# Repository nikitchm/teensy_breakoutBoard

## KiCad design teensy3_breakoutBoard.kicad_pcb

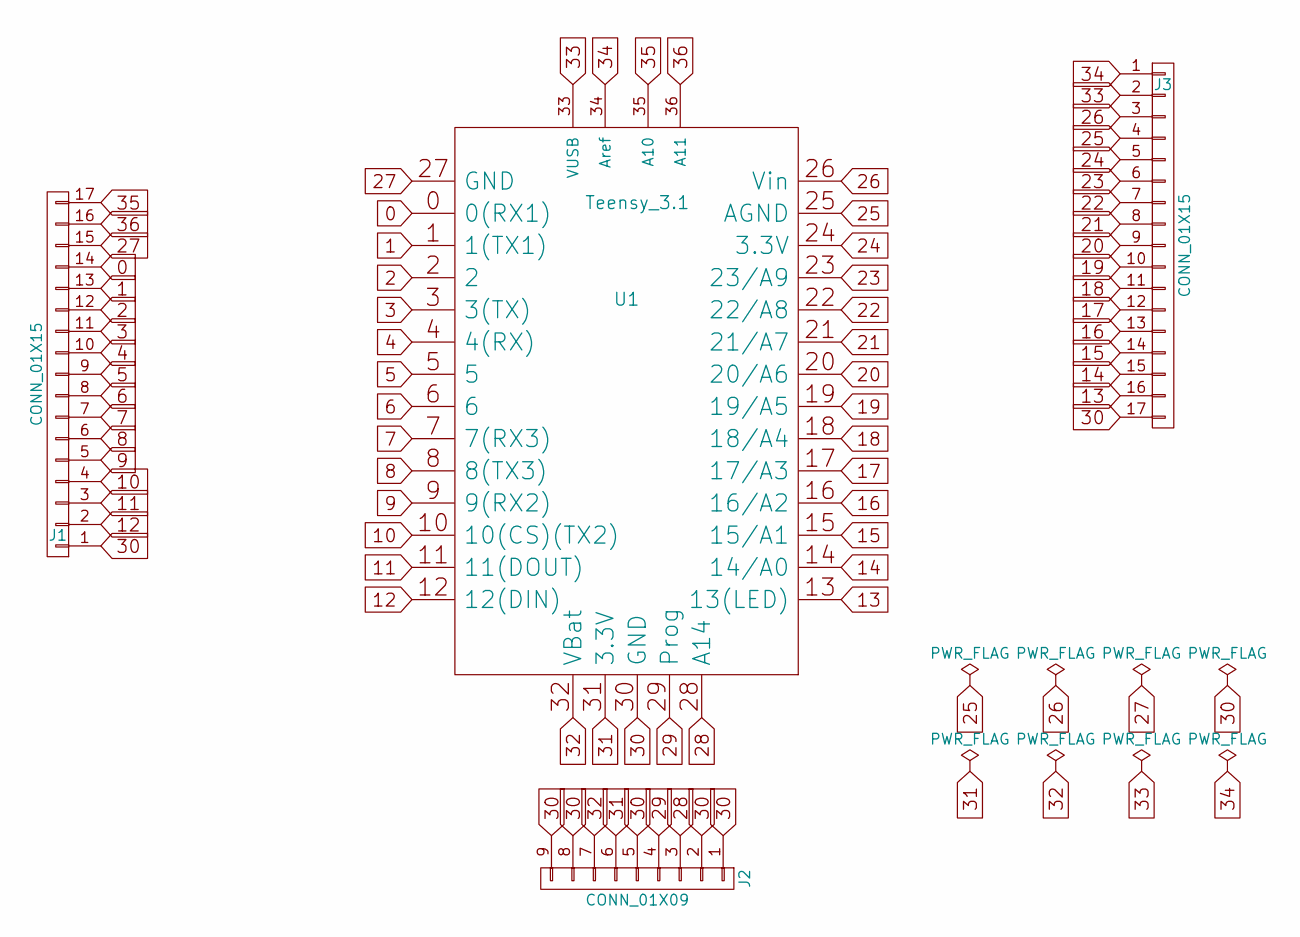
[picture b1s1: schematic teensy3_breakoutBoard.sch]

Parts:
J1, J3: CONN_01X15; Pin_Header_Straight_1x17_Pitch2.54mm
J2: CONN_01X09; Pin_Header_Straight_1x09_Pitch2.54mm
U1: Teensy_3.1; Teensy-3.1

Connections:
0: J1.14, U1.0 (0(RX1))
1: J1.13, U1.1 (1(TX1))
2: J1.12, U1.2
3: J1.11, U1.3 (3(TX))
4: J1.10, U1.4 (4(RX))
5: J1.9, U1.5
6: J1.8, U1.6
7: J1.7, U1.7 (7(RX3))
8: J1.6, U1.8 (8(TX3))
9: J1.5, U1.9 (9(RX2))
10: J1.4, U1.10 (10(CS)(TX2))
11: J1.3, U1.11 (11(DOUT))
12: J1.2, U1.12 (12(DIN))
13: J3.16, U1.13 (13(LED))
14: J3.15, U1.14 (14/A0)
15: J3.14, U1.15 (15/A1)
16: J3.13, U1.16 (16/A2)
17: J3.12, U1.17 (17/A3)
18: J3.11, U1.18 (18/A4)
19: J3.10, U1.19 (19/A5)
20: J3.9, U1.20 (20/A6)
21: J3.8, U1.21 (21/A7)
22: J3.7, U1.22 (22/A8)
23: J3.6, U1.23 (23/A9)
24: J3.5, U1.24 (3.3V)
25: J3.4, U1.25 (AGND)
26: J3.3, U1.26 (Vin)
27: J1.15, U1.27 (GND)
28: J2.3, U1.28 (A14)
29: J2.4, U1.29 (Prog)
30: J1.1, J2.1, J2.2, J2.5, J2.8, J2.9, J3.17, U1.30 (GND)
31: J2.6, U1.31 (3.3V)
32: J2.7, U1.32 (VBat)
33: J3.2, U1.33 (VUSB)
34: J3.1, U1.34 (Aref)
35: J1.17, U1.35 (A10)
36: J1.16, U1.36 (A11)

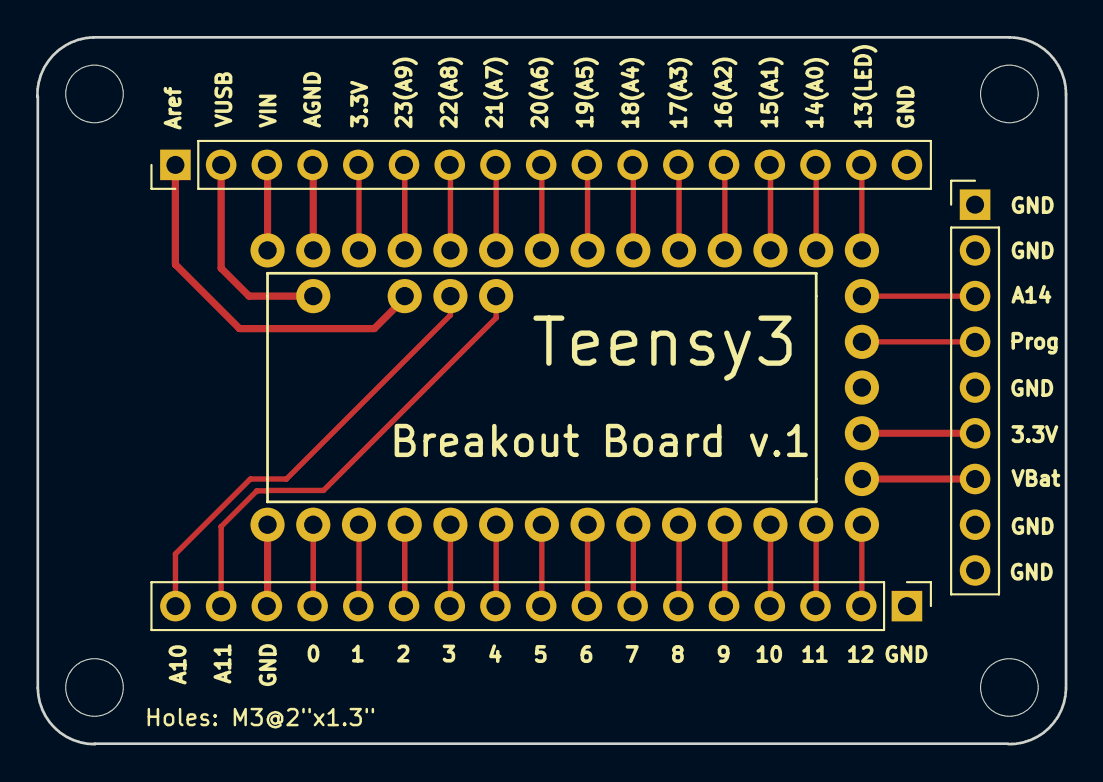
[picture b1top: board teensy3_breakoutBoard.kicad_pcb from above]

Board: 2 copper layers, 57.2 x 39.3 mm, 4 parts (0 on the bottom side), 37 nets.

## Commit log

2017-10-06 The project is completed, but not tested.
2017-10-06 Added the MIT license from GitHub.
